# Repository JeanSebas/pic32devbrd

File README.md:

# pic32devbrd

A general purpose development board for the PIC32MX250F128B microcontroller. Please see the [wiki] (https://github.com/irwineffect/pic32devbrd/wiki) for more information.

#Features:
* Onboard 3.3V switching regulator, designed to be powered off of the USB port
* PTC fuse to protect from short-circuit
* Onboard FTDI chip
* Power indication LED
* Tx/Rx LEDs
* General-purpose LED

---

Also, you should check out the [SUBLIBinal library](https://github.com/PalouseRobosub/SUBLIBinal), an efficient interrupt-driven library designed for boards using this microcontroller.

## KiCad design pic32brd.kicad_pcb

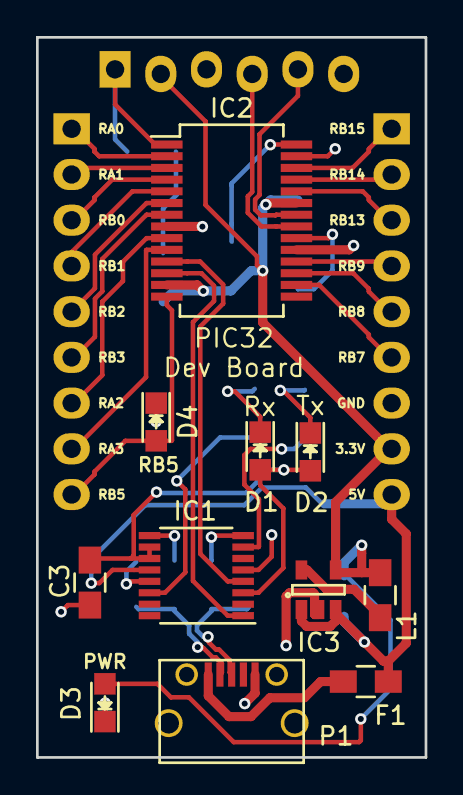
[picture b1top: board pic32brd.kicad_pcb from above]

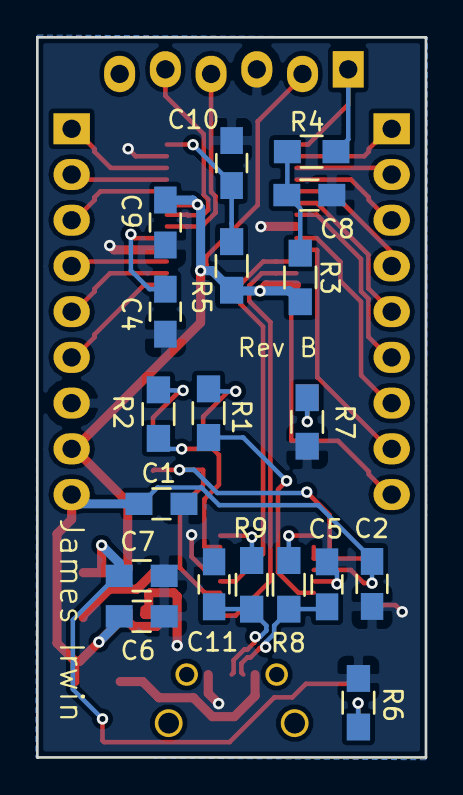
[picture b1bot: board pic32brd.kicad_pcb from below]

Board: 2 copper layers, 21.6 x 40.0 mm, 33 parts (19 on the bottom side), 39 nets.

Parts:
C1, C3, C8, C9, C10: 100n; C_0805_HandSoldering
C2, C6: 4.7u; C_0805_HandSoldering
C4, C7: 10u; C_0805_HandSoldering
C5, C11: 47p; C_0805_HandSoldering
Con1: prog_header; Pin_Header_Staggered_1x06
D1: TX; LED_0805
D2: RX; LED_0805
D3: PWR; LED_0805
D4: RB5; LED_0805
F1: PTC Fuse; C_0805_HandSoldering
IC1: FT230X; SSOP-16_3.9x4.9mm_Pitch0.635mm
IC2: PIC32MX2xx/1xx; SSOP-28_5.3x10.2mm_Pitch0.65mm
IC3: LM3671; SOT-23-5
L1: 2.2u; C_0805_HandSoldering
P1: USB_OTG; USB-MICRO-B
P2, P3: CONN_01X09; Pin_Header_Straight_1x09
R1, R2, R6, R7: 270; R_0805_HandSoldering
R3: 10k; R_0805_HandSoldering
R4: 1k; R_0805_HandSoldering
R5: 10; R_0805_HandSoldering
R8, R9: 27; R_0805_HandSoldering

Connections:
/D+: C11.1, P1.3, R9.2
/D-: C5.1, P1.2, R8.1
/FTDI/3V3_IO: C3.1, D1.2, D2.2, IC1.3, IC1.10, IC1.11
/FTDI/5V0: C1.1, C2.1, C6.1, F1.1, IC1.12, IC3.1, IC3.3, P3.9
/FTDI/FRX: IC1.4, IC2.11
/FTDI/FTX: IC1.1, IC2.12
/FTDI/GND: C1.2, C2.2, C3.2, C4.2, C5.2, C6.2, C7.2, C8.2, C9.2, C10.2, C11.2, Con1.3, IC1.5, IC1.13, IC2.8, IC2.19, IC2.27, IC3.2, P1.5, P3.7, R6.2, R7.2
/FTDI/RXLED: IC1.7, R2.2
/FTDI/TXLED: IC1.14, R1.2
/FTDI/USBD+: IC1.8, R9.1
/FTDI/USBD-: IC1.9, R8.2
/SWREG_5to3V3/3V3: C7.1, C9.1, Con1.2, D3.2, IC2.13, IC2.23, IC3.4, L1.1, P3.8, R3.1, R5.2
/microcontroller/AVDD: C10.1, IC2.28, R5.1
/microcontroller/PGC: Con1.5, IC2.22
/microcontroller/PGD: Con1.4, IC2.21
/microcontroller/RA0: IC2.2, P2.1
/microcontroller/RA1: IC2.3, P2.2
/microcontroller/RA2: IC2.9, P2.7
/microcontroller/RA3: IC2.10, P2.8
/microcontroller/RB0: IC2.4, P2.3
/microcontroller/RB1: IC2.5, P2.4
/microcontroller/RB2: IC2.6, P2.5
/microcontroller/RB3: IC2.7, P2.6
/microcontroller/RB5: D4.2, IC2.14, P2.9
/microcontroller/RB7: IC2.16, P3.6
/microcontroller/RB8: IC2.17, P3.5
/microcontroller/RB9: IC2.18, P3.4
/microcontroller/RB13: IC2.24, P3.3
/microcontroller/RB14: IC2.25, P3.2
/microcontroller/RB15: IC2.26, P3.1
/microcontroller/~MCLR: Con1.1, IC2.1, R4.1
unnamed: C4.1, IC2.20
unnamed: C8.1, R3.2, R4.2
unnamed: D1.1, R1.1
unnamed: D2.1, R2.1
unnamed: D3.1, R6.1
unnamed: D4.1, R7.1
unnamed: F1.2, P1.1
unnamed: IC3.5, L1.2

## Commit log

2015-12-03 added initial files
    might need to add library files, idk
2016-02-20 rev A
2016-03-13 finished revA backup
2016-03-19 Rev B
    added USB termination, swapped D+ and D- lines to be correct, and re-routed the board
2016-04-02 copied revB files to own folder
2016-04-02 swapped Tx and Rx silkscreen labels also moved LED labels on schematic so Rx is still red and Tx is yellow the bug was that LED labeling was from FTDI chip's perspective, not the microcontroller's pe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
2016-04-26 updated bom for revB
2016-04-26 added schematics for boards
2016-04-26 added digikey bom for boards
2016-04-26 added license
